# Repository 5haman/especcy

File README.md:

# Speccy micro

**A thumb-sized ESP32 handheld for ZX Spectrum games: 24 × 38 × 12 mm, designed from case to firmware.**

<p align="center"><sub>Concept visual based on the CAD model. The device has not been built yet.</sub></p>

Especcy explores how small a playable ZX Spectrum handheld can be. An ESP32-WROOM-32E module, a 0.85-inch 128 × 128 LCD, six buttons and a USB power socket fit in a two-part case. The repository holds the complete digital design:

- **Mechanical:** a scripted FreeCAD model with 47 components, automatic collision and envelope checks, STEP/STL/GLB exports and a Blender presentation.
- **Electrical:** KiCad 10 schematics for the carrier board and its programming fixture. Python generates them, every ERC rule passes, and the BOMs name exact parts.
- **Firmware:** a cycle-timed Spectrum 48K emulator in C++14 for ESP-IDF, with a GC9107 LCD driver, debounced controls and a pause menu.
- **Documentation:** 38 requirements with traceability, 17 verification scenarios, decision and risk registers, and an eight-page [product prospectus](docs/prospectus/speccy-micro-prospectus.pdf).

## Engineering highlights

- **Accurate 48K timing.** Each frame runs 69,888 T-states in 19,968 µs (about 50.08 Hz), with the 48K memory and I/O contention pattern. Instruction overshoot carries into the next frame, so emulated time does not drift.
- **256 × 192 pixels on a 128 × 128 screen.** The renderer averages each 2 × 2 block into one RGB565 pixel. The 128 × 96 picture sits between 16-row bands in the border colour. One 32 KiB DMA framebuffer feeds the LCD at about 25 fps.
- **A real game, with no bundled content.** The original *Dizzy* (1987) starts, walks and jumps in the host emulator. A 15,000-frame run is clean under AddressSanitizer and UndefinedBehaviorSanitizer. The repository ships only a project-authored diagnostic; offline tools convert your own snapshots.
- **Radios off by construction.** The firmware links no Wi-Fi, Bluetooth or PSRAM component, and it fails to compile if their configuration returns.
- **Generated, cross-checked hardware.** `design.py` drives the KiCad schematics and board. The checker matches every pin, part number and BOM row against the firmware GPIO map, and three deliberately miswired netlists must fail.
- **Open problems stay visible.** The study records its thermal and fit gates: the 560 mA supply budget gives 0.952 W of regulator loss at 5 V, and DRC keeps one known USB-stake/switch conflict on record.

## Gallery

<table>
  <tr>
    <td width="50%"></td>
    <td width="50%"></td>
  </tr>
  <tr>
    <td>Six layers: front shell, button plungers, LCD, carrier with switches, ESP32 module and rear shell. Concept visual.</td>
    <td>Carrier placement from KiCad: six switches, the regulator and the LCD wire pads around the WROOM module.</td>
  </tr>
  <tr>
    <td></td>
    <td></td>
  </tr>
  <tr>
    <td>The complete case beside a bare ESP32 DevKitC V4 board at the same scale. CAD render.</td>
    <td>Underside: the Micro-B power socket and six contacts for an external UART programming fixture. Concept visual.</td>
  </tr>
</table>

The [carrier schematic](hardware/electronics/previews/carrier.svg) and [fixture schematic](hardware/electronics/previews/fixture.svg) are also available as SVG.

## Status

The digital design is complete and checked. Building and testing a physical prototype is the next step.

| Area | State | Evidence |
| --- | --- | --- |
| Enclosure CAD | Done | 47 valid solids, no primary collisions, 24 × 38 × 12 mm envelope; valid STEP and eight closed STL meshes |
| Firmware | Ready for bench tests | Three sanitizer test suites pass; diagnostic and Dizzy images build with ESP-IDF v5.4.4 |
| Schematics and BOMs | Done | Carrier and fixture are ERC-clean with all rules; firmware, BOM and netlist agree |
| PCB layout | Placement only | Routing waits for measured parts; DRC keeps one known USB/switch conflict |
| Physical prototype | Not built | LCD, controls, real-time speed, heat, fit and programming need hardware tests |

The [roadmap](docs/roadmap.md) lists the open gates, and [verification](docs/verification.md) records every check that has run.

## Try it without hardware

You need CMake, a C++14 compiler and Python 3. No ROM or game is needed: the build generates its own diagnostic content.

```sh
cmake -S firmware -B firmware/build-host -DSPECCY_HOST=ON -DCMAKE_BUILD_TYPE=Debug
cmake --build firmware/build-host
ctest --test-dir firmware/build-host --output-on-failure

cd firmware/build-host
./speccy-host --rom content/spectrum48.rom --snapshot content/game48.sna \
  --frames 50 --buttons 9 --output frame.ppm
python3 ../tools/ppm_to_png.py frame.ppm frame.png --scale 4
```

The last two commands make this frame: the diagnostic test card as the emulator sends it to the 128 × 128 LCD, scaled 4×. The border is blue because the diagnostic copies the low three bits of the Kempston mask to the border port; `--buttons 9` holds Right and Up.

- **ESP32 firmware:** install ESP-IDF v5.4.4 and run `idf.py -B build-esp32 build` in `firmware/`. The [firmware guide](firmware/README.md) covers wiring, flashing, game content and the bench checklist.
- **Electrical study:** `python3 hardware/electronics/check.py` checks the stored results; the [electrical guide](hardware/electronics/README.md) rebuilds them with KiCad.
- **CAD:** the [development guide](docs/development.md) rebuilds the models, renders, export checks and the downloadable CAD package with FreeCAD and Blender.

<br clear="right">

## Design baseline

| Item | Selection |
| --- | --- |
| Processor | ESP32-WROOM-32E-N4 (4 MB flash, no PSRAM) on a custom 20.8 × 34.8 mm carrier |
| Display | Waveshare 0.85-inch LCD, SKU 26117: GC9107, 128 × 128, 3.3 V SPI; connector replaced by eight wires |
| Picture | 2 × 2 averaging to 128 × 96, centred between 16-row border bands |
| Controls | Up, Down, Left, Right, Fire (Kempston) and Menu (Resume/Restart) |
| Power | Micro-B, power only; TLV75733P 3.3 V LDO with a resettable fuse and TVS diode |
| Programming | External UART fixture on six underside pads; manual BOOT and RESET |
| Case | Two halves, 24 × 38 × 11.6 mm; 12 mm including button caps |
| Excluded | Battery, SD card, speaker, keyboard, Wi-Fi and Bluetooth |

## Repository layout

```text
firmware/              ESP-IDF project, shared emulator core, host runner, tests and tools
  common/              Spectrum 48K machine, video scaling, controls and menu (host and ESP32)
  main/                ESP32 entry point, GC9107 SPI driver, frame pacing and UART reports
  host/                Headless runner that writes PPM frames and JSON metrics
  tests/               CTest suites: runtime, command line and snapshot converter
  tools/               Content packaging, Z80-to-SNA conversion and PPM-to-PNG export
  vendor/              Pinned z80cpp core and the Waveshare driver notice
hardware/cad/          FreeCAD and Blender scripts, models, meshes, renders and check reports
hardware/electronics/  KiCad carrier and fixture, BOMs, generator, checks, reports and previews
docs/                  Requirements, architecture, verification, decisions, risks and prospectus
.github/workflows/     CI: host tests on GCC and Clang, ESP32 build, electrical and link checks
```

## Documentation

- [Product prospectus (PDF)](docs/prospectus/speccy-micro-prospectus.pdf): an eight-page visual introduction.
- [Documentation index](docs/README.md): the full engineering suite and reading paths.
- [Firmware guide](firmware/README.md), [electrical guide](hardware/electronics/README.md) and [CAD notes](hardware/cad/README.md).
- [Requirements](docs/requirements.md), [verification](docs/verification.md), [decisions](docs/decisions.md) and [risks](docs/risks.md).

## License

Copyright © 2026 Serhii Shyman. Each kind of file has its own license:

| Files | License |
| --- | --- |
| Source code and scripts: `firmware/`, every `*.py` file and `.github/` | [GPL-3.0](LICENSE) |
| Hardware design files: everything else in `hardware/` (CAD models, meshes, KiCad sources, BOMs, reports and previews) | [CERN-OHL-S-2.0](LICENSE-HARDWARE) |
| Documentation and images: Markdown files, the rest of `docs/` and the PNG renders | [CC BY-SA 4.0](LICENSE-DOCS) |

Third-party files keep their own terms. The [z80cpp core](firmware/vendor/z80cpp/UPSTREAM.md) is GPLv3, the [Waveshare notice](firmware/vendor/waveshare/NOTICE) covers the adapted LCD start-up sequence, and the KiCad library snapshots use CC BY-SA 4.0 with the KiCad library exception ([notice](hardware/electronics/NOTICE)). The CERN-OHL-S source location is <https://github.com/5haman/especcy>.

The repository contains no Spectrum ROM, game, game screenshot or game firmware image. Use your own legally obtained files for local builds. This is an unofficial hobby project, not affiliated with the owners of the ZX Spectrum or *Dizzy*, or with the manufacturers named here.

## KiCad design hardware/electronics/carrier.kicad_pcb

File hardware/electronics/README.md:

# Carrier electrical and placement study

Revision A adds editable KiCad 10 carrier and manual-fixture schematics, exact part selections, an **unrouted** carrier, and reproducible checks. The WROOM, LCD, six control centres and existing enclosure geometry are preserved. This completes the authorized electrical study; physical acceptance and fabrication release remain open.

Open [the preview](previews/index.html) for placement views and schematic SVGs. Open `carrier.kicad_pro` or `fixture.kicad_pro` in KiCad to edit the native circuits. The fixture has a reference schematic only, with no fixture PCB or probe mechanics.

## Files and reproduction

| File | Purpose |
| --- | --- |
| [carrier.kicad_sch](carrier.kicad_sch), [carrier.kicad_pcb](carrier.kicad_pcb) | Power, reset, straps, six controls, LCD and pogo; two copper layers, no tracks or copper fills |
| [fixture.kicad_sch](fixture.kicad_sch) | Independent fixture rail, rail monitor, two gated UART directions, manual BOOT/RESET |
| [carrier BOM](carrier-bom.csv), [LCD BOM](assembly-bom.csv), [fixture BOM](fixture-bom.csv) | One row per reference with quantity, exact MPN, footprint, source and qualification notes; no supplier pricing or purchases |
| `Study.kicad_sym`, `Study.pretty`, library tables | Local symbol/footprint snapshots; custom switch, wire and pogo pads; see [NOTICE](NOTICE) |
| [carrier STEP](previews/carrier.step) | Native KiCad placement export with nominal component models; not a certified assembled enclosure |
| [reports](reports/electrical-checks.json) | Native netlists, complete ERC/DRC JSON, firmware/BOM checks, pin coordinates, fit and power findings |
| [design.py](design.py), [build.py](build.py), [check.py](check.py) | Design inputs, native generation and cross-artifact checks |

From the repository root:

```sh
python3 hardware/electronics/build.py
```

The checked tools are KiCad **10.0.6** and FreeCAD **1.1.4**. KiCad's Python needs `pcbnew` and `wx`; FreeCAD's Python needs `FreeCAD` and `Part`. The generator otherwise uses the Python standard library. Defaults point to installed macOS applications. For another installation, set `SPECCY_KICAD_SHARE`, `SPECCY_KICAD_PYTHON` and `SPECCY_FREECAD_PYTHON`; make `kicad-cli` available and install its standard 3D models. No manufacturer documents are downloaded by the build.

Rebuilding replaces native files and generated reports. Preserve repeatable changes in `design.py` or the generator; direct KiCad edits remain valid for review but are overwritten on rebuild. `python3 hardware/electronics/check.py` checks existing netlists/BOMs/reports without generating them. Native board and STEP checks run as part of the full build.

The build checks both circuits with every ERC rule enabled and no exclusions. It checks exact pins/NCs/MPNs, firmware GPIOs, BOM parity and three deliberately incorrect netlists. It reopens the board, checks pad nets, original outline, sides, thickness and pogo access, then reopens both STEP exports. DRC is saved in full: **one shell-stake/courtyard conflict**, **70 unconnected items**, **zero schematic parity issues**. The checker requires that exact known conflict and rejects additional placement violations. Its successful exit means the study is reproduced and its gate is visible; it does not mean DRC or physical acceptance passed.

Serve the preview locally if needed:

```sh
python3 -m http.server 8790 --bind 127.0.0.1
```

Open `http://127.0.0.1:8790/hardware/electronics/previews/`. Safari inspection confirmed that all four SVG previews load.

## Carrier power and reset

J1 is GCT **USB3076-30-A**, Micro-B power only. D+/D−/ID are explicitly unconnected; the shell is grounded. Use a regulated, rated dedicated power source of at least 1 A. The circuit does not enumerate or negotiate USB host current. F1 is Bourns **MF-PSMF075X-2**, a 0.75 A resettable fuse, followed by an ESD shunt and TI **TLV75733PDBVR**. The LDO input and enable share `VBUS_FUSED`; output is 3.3 V. C1/C2 are 10 µF, 10 V X5R; C3 is a local 100 nF bypass at the module supply.

D1 **CDSOD323-T05C** has 5.0 V working peak, 6.0 V minimum breakdown and 9.8 V maximum clamp at 1 A. It does **not** protect the LDO's 5.5 V recommended / 6 V absolute input limit against sustained overvoltage. Limit the prototype source to 4.75–5.00 V at the TVS; reselect or qualify protection before using a wider input range. The 5.25 V sweep in the power report is a thermal boundary case outside this TVS rating. No system ESD result is claimed.

R1/C4 give EN a 10 kΩ pull-up and 1 µF capacitor. R2 pulls GPIO0/BOOT high; R3 and R4 hold GPIO2 and GPIO12 low. The latter preserves the module's 3.3 V flash selection. Other unused and flash-connected pins have explicit NC markers. Module ground pins 1/15/38/39 are on GND. The module footprint retains its ground-pad array with provisional 0.30 mm drills; its antenna keepout stays in DRC. Radios remain disabled.

## LCD and controls

J2 is a carrier wire-pad array, not a purchased connector. Its order matches the manufacturer's module schematic:

| Carrier pad | LCD signal | WROOM GPIO |
| --- | --- | --- |
| 1 | VCC / 3.3 V | Supply |
| 2 | GND | Ground |
| 3 | DIN | 23 |
| 4 | CLK | 18 |
| 5 | CS | 21 |
| 6 | DC | 22 |
| 7 | RST | 19 |
| 8 | BL | 25 |

Waveshare **26117** remains the selected GC9107 128 × 128 module. The manufacturer circuit has a backlight transistor; BL drives its base through 1 kΩ rather than supplying LED current directly. The module also includes its own regulator. Supply it with the specified 3.3 V. Its FAQ states up to 60 mA. Confirm the purchased revision's physical pad order after MX1.25 removal; source connector numbering alone does not prove solder-pad orientation.

SW1–SW6 are TE **2337228-2**, also named **USLPT3026EL2TR**: Up 26, Down 27, Left 32, Right 33, Fire 13, Menu 14. Each is active low to GND, using firmware pull-ups and 10 ms debounce. On the TE drawing, T1/T2 share one contact and T3/T4 share the other. The footprint numbers each pair 1 and 2 and keeps the central 1.60 × 2.60 mm free of pads, tracks, vias and fills.

## Programming contacts and fixture

Both placement views put USB at the bottom. In the **underside view**, pad 1 is leftmost. In the **front projection**, pad 1 is at CAD X = 15.75 and the numbering runs toward decreasing X. Do not copy the old generic CAD label's order. A probe carrier viewed from its contact tips must mirror the underside view; wire by number and continuity-test the mating pair.

| Pad | Device signal | Fixture connection |
| --- | --- | --- |
| 1 | GND | Common ground |
| 2 | 3V3_SENSE | High-impedance voltage sensing only; never a power input |
| 3 | UART_TX / GPIO1 | Buffer input → adapter RX |
| 4 | UART_RX / GPIO3 | Buffer output ← adapter TX |
| 5 | EN | Manual RESET switch to ground |
| 6 | BOOT / GPIO0 | Manual BOOT switch to ground |

J3 pad centres are 1.50 mm apart at CAD Y = **8.25**. This is 0.20 mm forward of the old generic pads and stays within the unchanged opening. Pads are 1.05 × 1.50 mm with no paste. Exact probes, contact force, alignment and mating sequence remain a physical gate.

The handheld receives power through Micro-B. Fixture J2 pin 1 (adapter VCC) is **NC**. Its other pins are logical GND/TX/RX, not a universal adapter cable pinout. Fixture J3 accepts its **own regulated 3.3 V ±5% rail** with common ground. That rail powers the fixture circuitry only and has no connection to device pad 2. A controller's regulated rail or a separate regulated bench source can supply it; do not obtain it from the handheld sense pad. Use a 3.3 V logic UART adapter.

TI **SN74LVC2G125DCUR** buffers both UART directions. Both active-low enables have a pull-up and share the open-drain output of **TLV7041DBVR**. A 523 kΩ / 1 MΩ divider senses the handheld; **LM4040A20IDBZR** supplies a 2.048 V reference. External feedback adds hysteresis to the comparator's internal hysteresis. The nominal enable/disable points are about **3.14 / 3.08 V**; the [analysis](reports/fixture-analysis.json) records assumptions and variation. Sense-divider current is about **2.17 µA at 3.3 V**. The comparator inputs tolerate 7 V while unpowered; the buffer has `Ioff` protection. R8/R9 define buffer input levels when an adapter or device is absent.

With the device rail absent, the enable pull-up keeps both buffer outputs high impedance. Manual BOOT/RESET only sink to GND. Confirm actual output levels, leakage and ramp/brownout behavior on hardware; static topology and datasheet limits do not prove every transient sequence.

Manual sequence after circuit/continuity review:

1. With device USB off, mate the numbered contacts and connect common ground, the local fixture rail and UART. Confirm device pad 2 is not driven.
2. Apply qualified Micro-B power. Hold BOOT, pulse RESET low for at least 10 ms, release RESET, then start esptool. Keep BOOT low through reset and the manufacturer's 1 ms strap-hold interval.
3. Use esptool's `--before no_reset --after no_reset` settings; DTR/RTS have no circuit here. Use the built mode's bootloader at `0x1000`, partitions at `0x8000` and app at `0x10000`, as described in the [firmware guide](../../firmware/README.md).
4. Release BOOT after esptool connects. After a complete flash, pulse RESET with BOOT released to run. Interrupted programming or invalid content uses the same manual bootloader entry and full reflash.

Required bench cases remain: cold boot; BOOT/RESET and normal flash; USB present/absent with fixture and adapter powered/unpowered; disconnected contacts; brownout; interrupted flash; invalid-content recovery; complete return to execution. Record device 3V3, both UART directions, EN/BOOT and off-state currents.

## Fit and thermal gates

The carrier follows the native `CarrierPCB` outline, including corner reliefs and the antenna cutout. Nominal blank size stays 20.8 × 34.8 × 0.8 mm; the cut/rounded native solid's Y extent is 34.769694 mm. KiCad's board-only STEP exports a **0.71 mm dielectric core**; copper/mask layers complete the nominal 0.8 mm stack. The report aligns the core within CAD Z = 4.8–5.6. Its 0.5 mm grid containment check supplements the exact native-board outline check; it is not a tolerance certification. Selected package envelopes show no intersection with the unchanged case/LCD solids in the checked nominal model.

| Gate | Evidence and required follow-up |
| --- | --- |
| Button actuation | TE recommends a 1.00 mm pressing tip, alignment ≤0.20 mm. Existing stems are 1.80 mm. Nominal switch top Z = 6.25 leaves only 0.05 mm to the stem at 6.30; general drawing tolerance permits Z = 6.45, giving 0.15 mm preload/interference, equal to nominal travel. Trial exact switches and actuation before revising geometry. |
| USB/Down switch | GCT 1.00 mm nominal stakes protrude 0.20 mm through the nominal 0.80 mm board, potentially 0.40 mm with drawing tolerance before PCB variation. DRC retains one stake inside SW2's courtyard. Verify contact, solder, tolerances and assembly; if it fails, explicitly revisit the socket or geometry choice. |
| USB opening | Selected socket origin X = 12.35, Y = 4.25 puts its nominal mouth at Y = 0.30. Its maximum width reaches the opening edge with zero lateral margin. Cable overmold access is unmeasured. |
| LCD and wires | Rear heights, physical pads, removal/rework and wire access remain unmeasured. No connector-clearance or assembly-order claim follows from this study. |
| LDO heat | A supply-capability budget of 500 mA ESP32 + 60 mA LCD gives 0.952 W loss at 5 V. It is not measured consumption. TI's DBV reference θJA values are 100.8 °C/W on the EVM and 231.1 °C/W on its JEDEC board; neither establishes this carrier/enclosure. At 5.25 V/560 mA/25 °C, even the EVM arithmetic gives 135.1 °C versus 125 °C recommended maximum. Measure enclosure current, transients and temperature with margin before routing/release. |
| Fuse and protection | Hold current falls to 570 mA at 50 °C and 530 mA at 60 °C. Check local self-heating and sustained current. The selected 5 V TVS also limits the qualified source range; it is not overvoltage protection. |
| Remaining qualification | Verify passive DC-bias capacitance, actual package tolerances, stock/ordering codes, probe mechanics, fabrication process and fasteners. The 10 µF Murata sheet permits ±0.15 mm in length/width/height; maxima are used here. Other passive envelopes use family allowances pending selected-part qualification. |

If the selected LDO cannot meet thermal limits, return that result for an explicit power-strategy decision. Do not treat its 1 A electrical rating, thermal shutdown or a nominal box fit as continuous-load acceptance. No enclosure, legacy CAD exports, firmware, game content, routed PCB or fabrication package is changed by this phase.

Sources and document hashes are in [sources.json](reports/sources.json), with the cross-project references in [research](../../docs/research.md). Full manufacturer PDFs remain outside the repository.

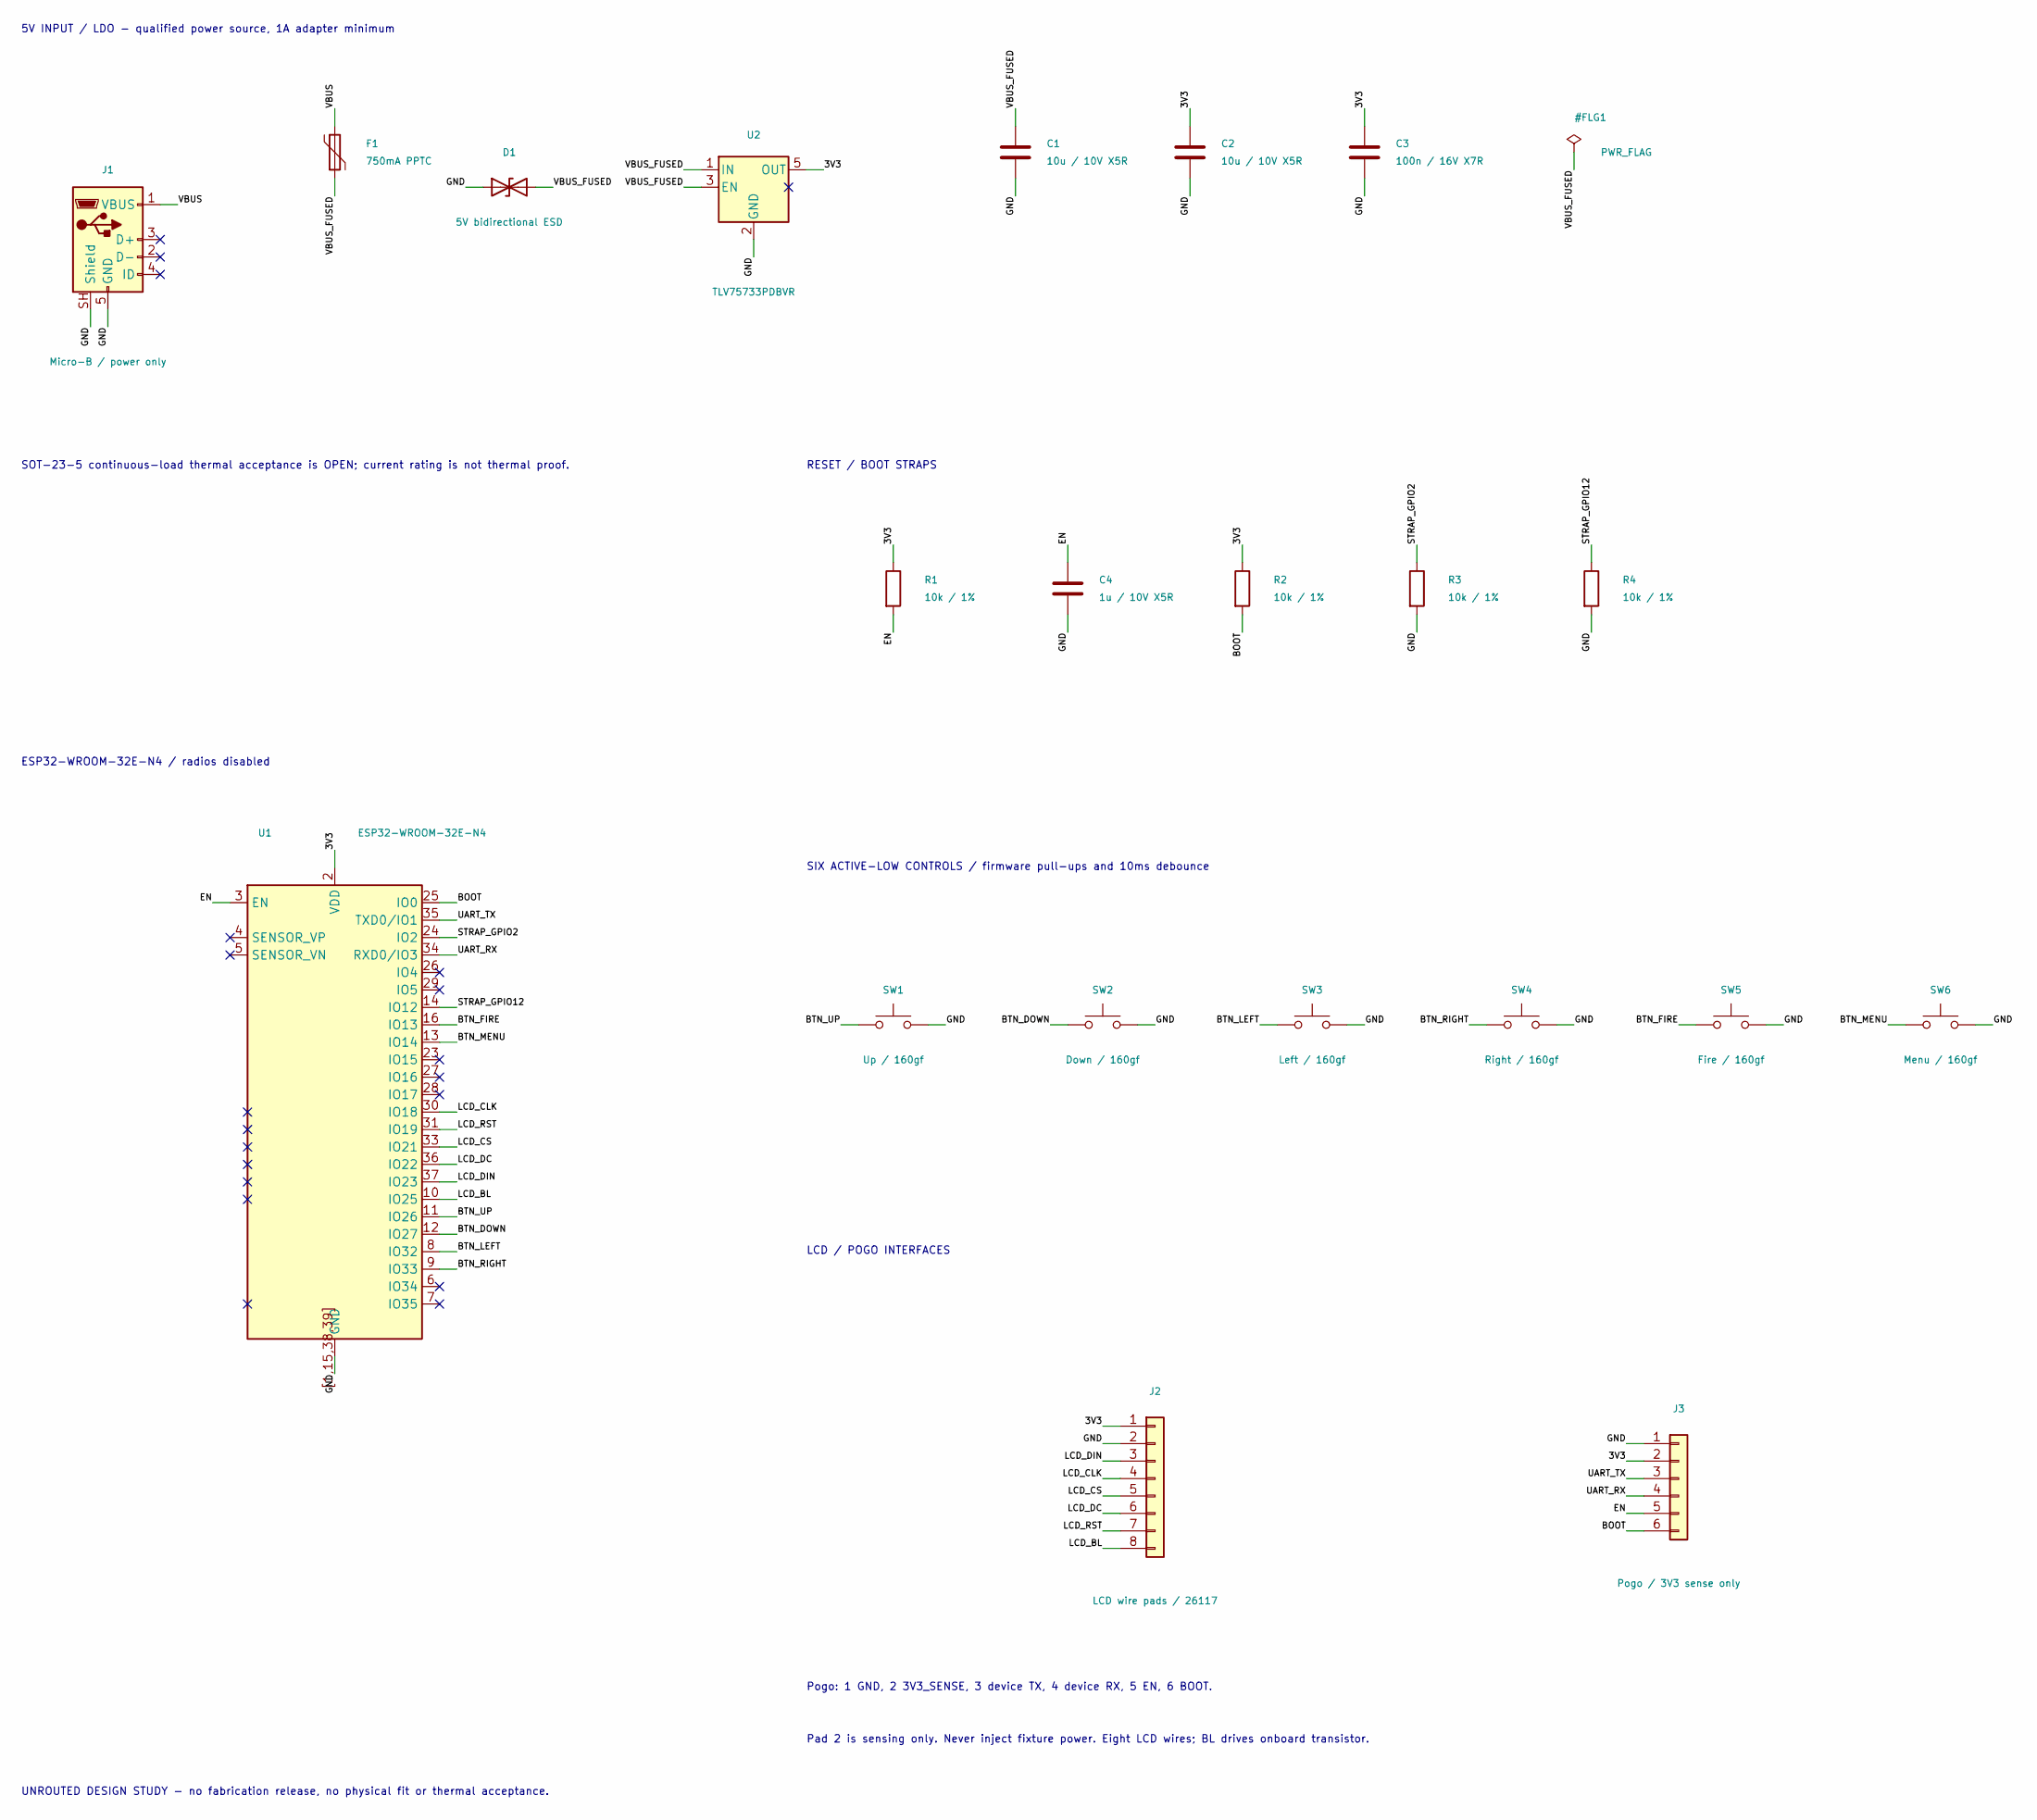
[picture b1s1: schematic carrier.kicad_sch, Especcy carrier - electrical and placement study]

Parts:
C1, C2: 10u / 10V X5R; C0603; MPN GRM188R61A106KE69D
C3: 100n / 16V X7R; C0402; MPN GRM155R71C104KA88D
C4: 1u / 10V X5R; C0402; MPN GRM155R61A105KE15D
D1: 5V bidirectional ESD; TVS; MPN CDSOD323-T05C
F1: 750mA PPTC; Fuse; MPN MF-PSMF075X-2
J1: Micro-B / power only; USB; MPN USB3076-30-A
J2: LCD wire pads / 26117; LCDPads; MPN PCB feature
J3: Pogo / 3V3 sense only; PogoPads; MPN PCB feature
R1, R2, R3, R4: 10k / 1%; R0402; MPN RC0402FR-0710KL
SW1: Up / 160gf; TESwitch; MPN 2337228-2
SW2: Down / 160gf; TESwitch; MPN 2337228-2
SW3: Left / 160gf; TESwitch; MPN 2337228-2
SW4: Right / 160gf; TESwitch; MPN 2337228-2
SW5: Fire / 160gf; TESwitch; MPN 2337228-2
SW6: Menu / 160gf; TESwitch; MPN 2337228-2
U1: ESP32-WROOM-32E-N4; ESP32; MPN ESP32-WROOM-32E-N4
U2: TLV75733PDBVR; SOT23_5; MPN TLV75733PDBVR

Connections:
/3V3: C2.1, C3.1, J2.1, J3.2, R1.1, R2.1, U1.2 (VDD), U2.5 (OUT)
/BOOT: J3.6, R2.2, U1.25 (IO0)
/BTN_DOWN: SW2.1, U1.12 (IO27)
/BTN_FIRE: SW5.1, U1.16 (IO13)
/BTN_LEFT: SW3.1, U1.8 (IO32)
/BTN_MENU: SW6.1, U1.13 (IO14)
/BTN_RIGHT: SW4.1, U1.9 (IO33)
/BTN_UP: SW1.1, U1.11 (IO26)
/EN: C4.1, J3.5, R1.2, U1.3 (EN)
/GND: C1.2, C2.2, C3.2, C4.2, D1.1 (A1), J1.5 (GND), J1.SH (Shield), J2.2, J3.1, R3.2, R4.2, SW1.2, SW2.2, SW3.2, SW4.2, SW5.2, SW6.2, U1.1, U1.15, U1.38, U1.39, U1.[1,15,38,39] (GND), U2.2 (GND)
/LCD_BL: J2.8, U1.10 (IO25)
/LCD_CLK: J2.4, U1.30 (IO18)
/LCD_CS: J2.5, U1.33 (IO21)
/LCD_DC: J2.6, U1.36 (IO22)
/LCD_DIN: J2.3, U1.37 (IO23)
/LCD_RST: J2.7, U1.31 (IO19)
/STRAP_GPIO2: R3.1, U1.24 (IO2)
/STRAP_GPIO12: R4.1, U1.14 (IO12)
/UART_RX: J3.4, U1.34 (RXD0/IO3)
/UART_TX: J3.3, U1.35 (TXD0/IO1)
/VBUS: F1.1, J1.1 (VBUS)
/VBUS_FUSED: C1.1, D1.2 (A2), F1.2, U2.1 (IN), U2.3 (EN)

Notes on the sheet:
5V INPUT / LDO - qualified power source, 1A adapter minimum
SOT-23-5 continuous-load thermal acceptance is OPEN; current rating is not thermal proof.
RESET / BOOT STRAPS
ESP32-WROOM-32E-N4 / radios disabled
SIX ACTIVE-LOW CONTROLS / firmware pull-ups and 10ms debounce
LCD / POGO INTERFACES
Pogo: 1 GND, 2 3V3_SENSE, 3 device TX, 4 device RX, 5 EN, 6 BOOT.
Pad 2 is sensing only. Never inject fixture power. Eight LCD wires; BL drives onboard transistor.
UNROUTED DESIGN STUDY - no fabrication release, no physical fit or thermal acceptance.

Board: 2 copper layers, 21 parts (5 on the bottom side), 22 nets, no tracks yet.

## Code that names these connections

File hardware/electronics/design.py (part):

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                placement, body, source='https://www.murata.com/en-global/products/capacitor/mlcc')


GPIO_NETS = {23: 'LCD_DIN', 18: 'LCD_CLK', 21: 'LCD_CS', 22: 'LCD_DC',
             19: 'LCD_RST', 25: 'LCD_BL', 26: 'BTN_UP', 27: 'BTN_DOWN',
             32: 'BTN_LEFT', 33: 'BTN_RIGHT', 13: 'BTN_FIRE', 14: 'BTN_MENU'}

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             (139.7, 93.98), (21.75, 22.6, 'F', 90)),
    resistor('R2', '10k / 1%', 'RC0402FR-0710KL', {1: '3V3', 2: 'BOOT'},
             (190.5, 93.98), (14.1, 8.1, 'F', 0)),
    resistor('R3', '10k / 1%', 'RC0402FR-0710KL', {1: 'STRAP_GPIO2', 2: 'GND'},
             (215.9, 93.98), (15.2, 10.7, 'F', 0)),
    resistor('R4', '10k / 1%', 'RC0402FR-0710KL', {1: 'STRAP_GPIO12', 2: 'GND'},
             (241.3, 93.98), (15.4, 9.5, 'F', 0)),
    part('U1', 'ESP32', 'ESP32-WROOM-32E-N4', 'ESP32-WROOM-32E-N4', 'Espressif', 'ESP32',
         {1: 'GND', 2: '3V3', 3: 'EN', 4: None, 5: None, 6: None, 7: None,
          8: 'BTN_LEFT', 9: 'BTN_RIGHT', 10: 'LCD_BL', 11: 'BTN_UP', 12: 'BTN_DOWN',
          13: 'BTN_MENU', 14: 'STRAP_GPIO12', 15: 'GND', 16: 'BTN_FIRE',
          17: None, 18: None, 19: None, 20: None, 21: None, 22: None, 23: None,
          24: 'STRAP_GPIO2', 25: 'BOOT', 26: None, 27: None, 28: None, 29: None,
          30: 'LCD_CLK', 31: 'LCD_RST', 32: None, 33: 'LCD_CS',
          34: 'UART_RX', 35: 'UART_TX', 36: 'LCD_DC', 37: 'LCD_DIN', 38: 'GND', 39: 'GND'},
         (58.42, 170.18), (12.0, 22.85, 'B', 0), [18.0, 25.5, 3.1],
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

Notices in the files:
README.md:
Software: GPL-3.0
Hardware: CERN-OHL-S-2.0
Docs: CC BY-SA 4.0
